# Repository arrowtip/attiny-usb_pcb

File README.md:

# ATtiny-USB PCB

Small pcb to allow ATtiny DIP-8 chips to communicate through USB.

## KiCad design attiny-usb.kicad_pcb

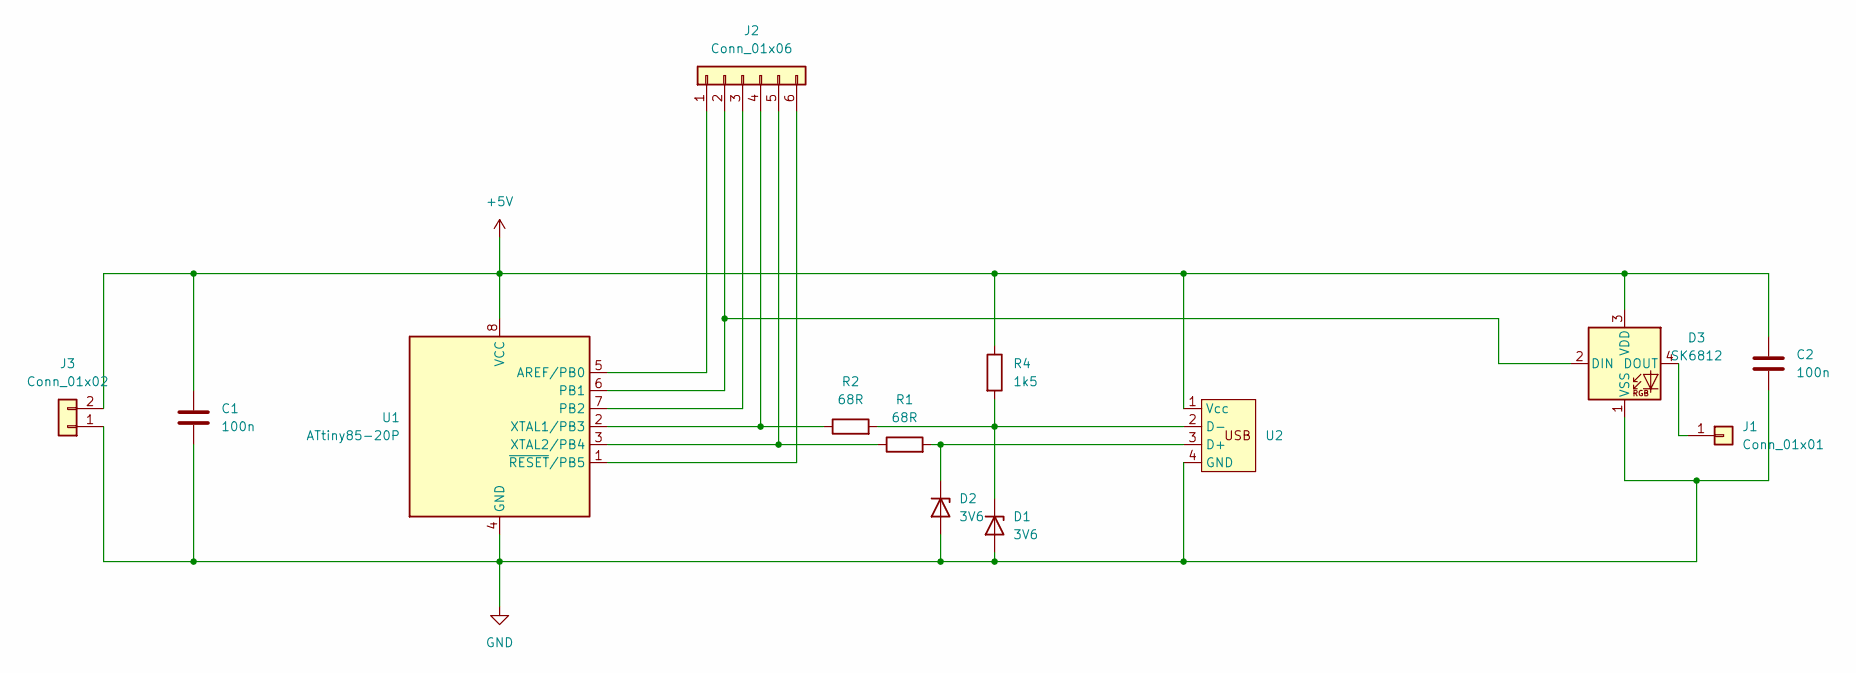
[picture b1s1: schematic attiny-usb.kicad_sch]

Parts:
C1, C2: 100n; C_0805_2012Metric_Pad1.18x1.45mm_HandSolder; JLC 0805
D1, D2: 3V6; D_SOD-123; JLC SOD-123
D3: SK6812; LED_SK6812_PLCC4_5.0x5.0mm_P3.2mm; JLC SMD5050-4P
J1: Conn_01x01; PinHeader_1x01_P2.54mm_Vertical
J2: Conn_01x06; PinHeader_1x06_P2.54mm_Vertical
J3: Conn_01x02; PinHeader_1x02_P2.54mm_Vertical
R1, R2: 68R; R_0805_2012Metric_Pad1.20x1.40mm_HandSolder; JLC 0805
R4: 1k5; R_0805_2012Metric_Pad1.20x1.40mm_HandSolder; JLC 0805
U1: ATtiny85-20P; DIP-8_W7.62mm
U2: pcb_usb-connector

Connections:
+5V: C1.1, C2.1, D3.3 (VDD), J3.2, R4.1, U1.8 (VCC), U2.1 (Vcc)
GND: C1.2, C2.2, D1.2 (A), D2.2 (A), D3.1 (VSS), J3.1, U1.4 (GND), U2.4 (GND)
unnamed: D1.1 (K), R2.2, R4.2, U2.2 (D-)
unnamed: D2.1 (K), R1.2, U2.3 (D+)
unnamed: D3.2 (DIN), J2.2, U1.6 (PB1)
unnamed: D3.4 (DOUT), J1.1
unnamed: J2.1, U1.5 (AREF/PB0)
unnamed: J2.3, U1.7 (PB2)
unnamed: J2.4, R2.1, U1.2 (XTAL1/PB3)
unnamed: J2.5, R1.1, U1.3 (XTAL2/PB4)
unnamed: J2.6, U1.1 (~RESET/PB5)

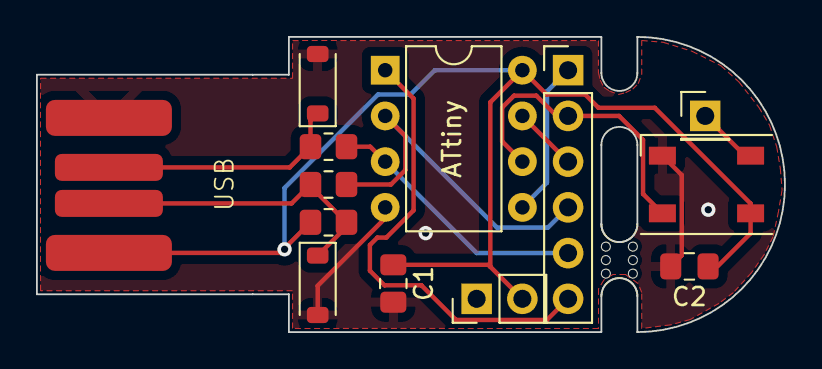
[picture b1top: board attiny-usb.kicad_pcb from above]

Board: 2 copper layers, 41.6 x 16.4 mm, 14 parts (0 on the bottom side), 11 nets.

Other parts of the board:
mouse-bite-2mm-slot: VAL**; mouse-bite-2mm-slot

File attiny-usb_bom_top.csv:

"Comment","Designator","Footprint","LCSC Part #"
"100n","C1 C2","1206","C525187"
"3V6","D1 D2","SOD-123","C2891771"
"SK6812","D3","SMD5050-4P","C5160656"
"Conn_01x05","J1","",""
"68R","R1 R2","0805","C17802"
"400R","R3","0805","C153298"
"1k5","R4","0805","C103998"
"ATtiny85-20P","U1","",""
"~","U2","",""

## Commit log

2023-10-05 init repository after major fuckup
2023-10-05 design new pcb
2023-10-05 create 2x3 panel
2023-10-05 add production directory for production output
2023-10-07 create pcb outline for version 2.0.0
    Thinking about moving large pin header one step towards the usb
    connector.
2023-10-08 move large pin header and remove resistor for Neopixel
2023-10-09 add mouse bite for neopixel
2023-10-09 route tracks. no errors
2023-10-09 create panel of 2x3
2023-10-09 add production directory to panel
2023-10-10 correct footprint of C1,C2 and add header for Neopixel output
    fixes #2
    fixes #3
2023-10-10 create panel for modified version
2023-10-10 removed all silkscreen references from half the boards in panel
